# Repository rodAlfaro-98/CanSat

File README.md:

# CanSat
CanSat chido final final este sí

## Integrantes

1.electrónica
  -Kevin L 
  -Takao K 
2.control
  -Rodrigo A 

3.mecánica
  -Roberto S 
  -Emmanuel Z 

## hardWare (sujeto a cambios)

-"GPS NEO6"
-"Arduino nano"
-"Arduino UNO"

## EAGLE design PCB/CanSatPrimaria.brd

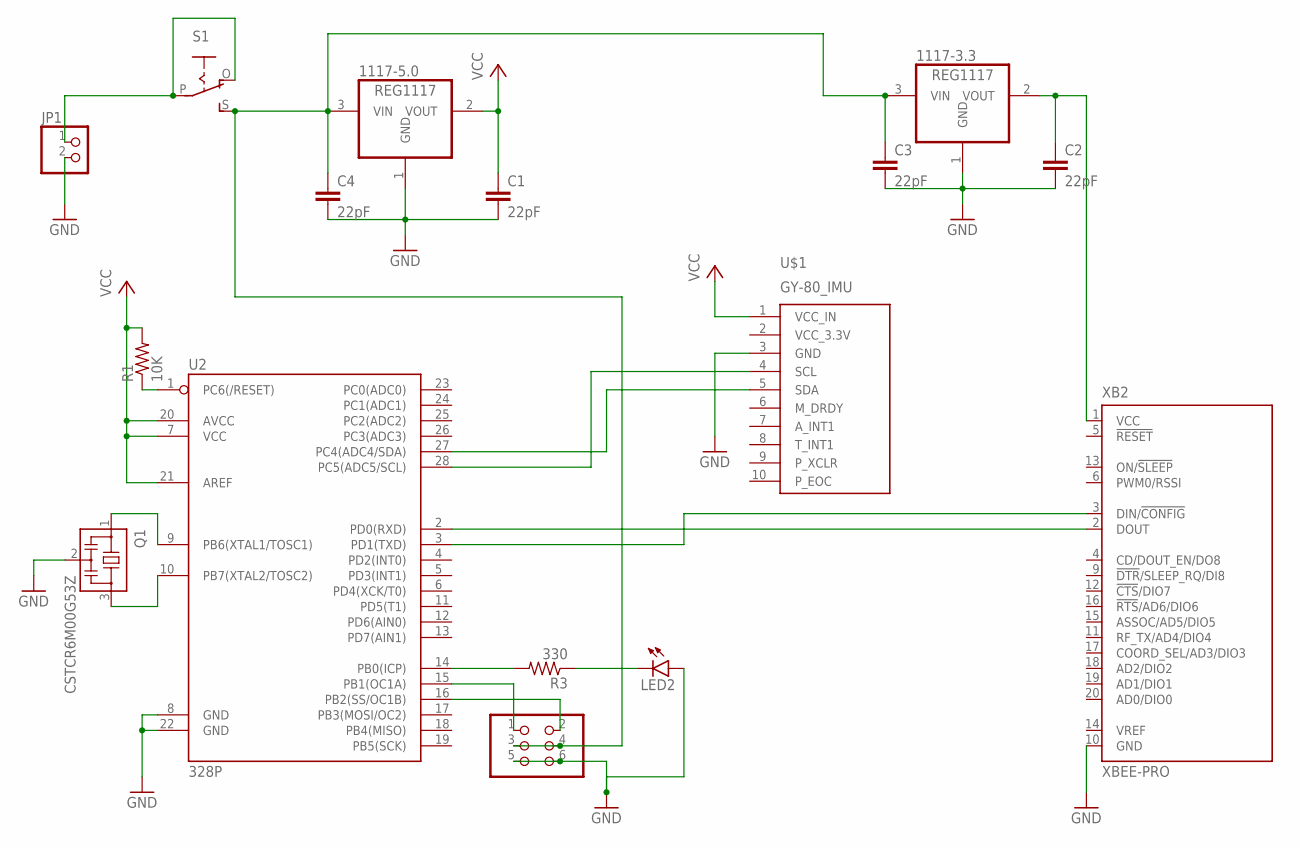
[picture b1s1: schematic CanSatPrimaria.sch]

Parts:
1117-3.3, 1117-5.0: REG1117; SOT223
C1, C2, C3, C4: 22pF; C1206
JP1: PINHD-1X2; 1X02
JP3: PINHD-2X3; 2X03
LED2: LEDCHIPLED_1206; CHIPLED_1206
Q1: CSTCR6M00G53Z; CSTCR6M
R1: 10K; M1206
R3: 330; M1206
S1: EG1218S; EG1218
U2: 328P; DIP28
U$1: GY-80_IMU; MA10-1
XB2: XBEE-PRO

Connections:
GND: 1117-3.3.1 (GND), 1117-5.0.1 (GND), C1.2, C2.2, C3.2, C4.2, JP1.2, JP3.5, JP3.6, LED2.A, Q1.2, U2.8 (GND), U2.22 (GND), U$1.3 (GND), XB2.10 (GND)
unnamed: 1117-3.3.2 (VOUT), C2.1, XB2.1 (VCC)
unnamed: Q1.1, U2.9 (PB6(XTAL1/TOSC1))
unnamed: U2.2 (PD0(RXD)), XB2.2 (DOUT)
unnamed: Q1.3, U2.10 (PB7(XTAL2/TOSC2))
unnamed: R1.1, U2.1 (PC6(/RESET))
unnamed: U2.27 (PC4(ADC4/SDA)), U$1.5 (SDA)
unnamed: U2.3 (PD1(TXD)), XB2.3 (DIN/!CONFIG)
unnamed: JP1.1, S1.O, S1.P
unnamed: U2.28 (PC5(ADC5/SCL)), U$1.4 (SCL)
unnamed: JP3.2, U2.16 (PB2(SS/OC1B))
unnamed: JP3.1, U2.15 (PB1(OC1A))
unnamed: R3.2, U2.14 (PB0(ICP))
unnamed: LED2.C, R3.1
unnamed: 1117-3.3.3 (VIN), 1117-5.0.3 (VIN), C3.1, C4.1, JP3.3, JP3.4, S1.S
VCC: 1117-5.0.2 (VOUT), C1.1, R1.2, U2.7 (VCC), U2.20 (AVCC), U2.21 (AREF), U$1.1 (VCC_IN)

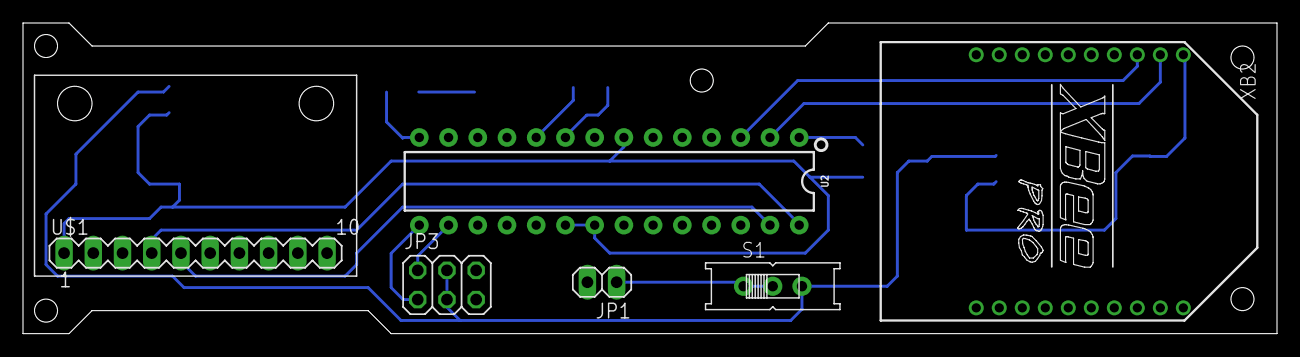
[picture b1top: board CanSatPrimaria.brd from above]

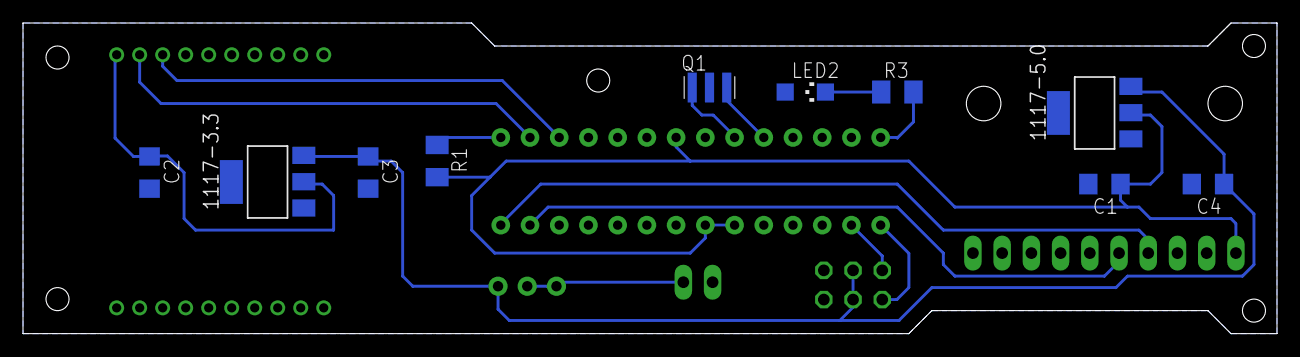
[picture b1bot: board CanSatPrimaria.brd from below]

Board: 2 copper layers, 109.0 x 27.0 mm, 16 parts (10 on the bottom side), 16 nets.

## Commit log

2020-01-10 Guia de Misión
2020-01-10 Borrador del documento a entregar.
2020-01-10 Documento a entregar.
2020-01-10 Codigos del Satélite y de Estación Terrena.
2020-01-14 gps sin interfaz
    instalar TinyGPS.h
2020-01-15 WIP
    arduino works, python not yet
2020-01-15 python works
2020-01-31 Formato para SolidWorks
2020-01-31 Pieza
2020-02-06 Se agregaron los archivos .py ya modularizado y con hilos (1 funcional, el otro en prueba)
2020-02-06 Hilos funcionando en python
2020-02-17 Librerías para sensores
2020-03-29 Tarjetas de la carga primaria y secundaria.

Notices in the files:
parts and their libraries:
SparkFun-IC-Microcontroller: Licensing: Creative Commons ShareAlike 4.0 International - https://creativecommons.org/licenses/by-sa/4.0
